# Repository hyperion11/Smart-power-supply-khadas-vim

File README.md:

# Smart-power-supply-khadas-vim
smart power supply for carpc based on khadas vim1 and rtd2662 scaler

https://youtu.be/VpjinB8Rm2o

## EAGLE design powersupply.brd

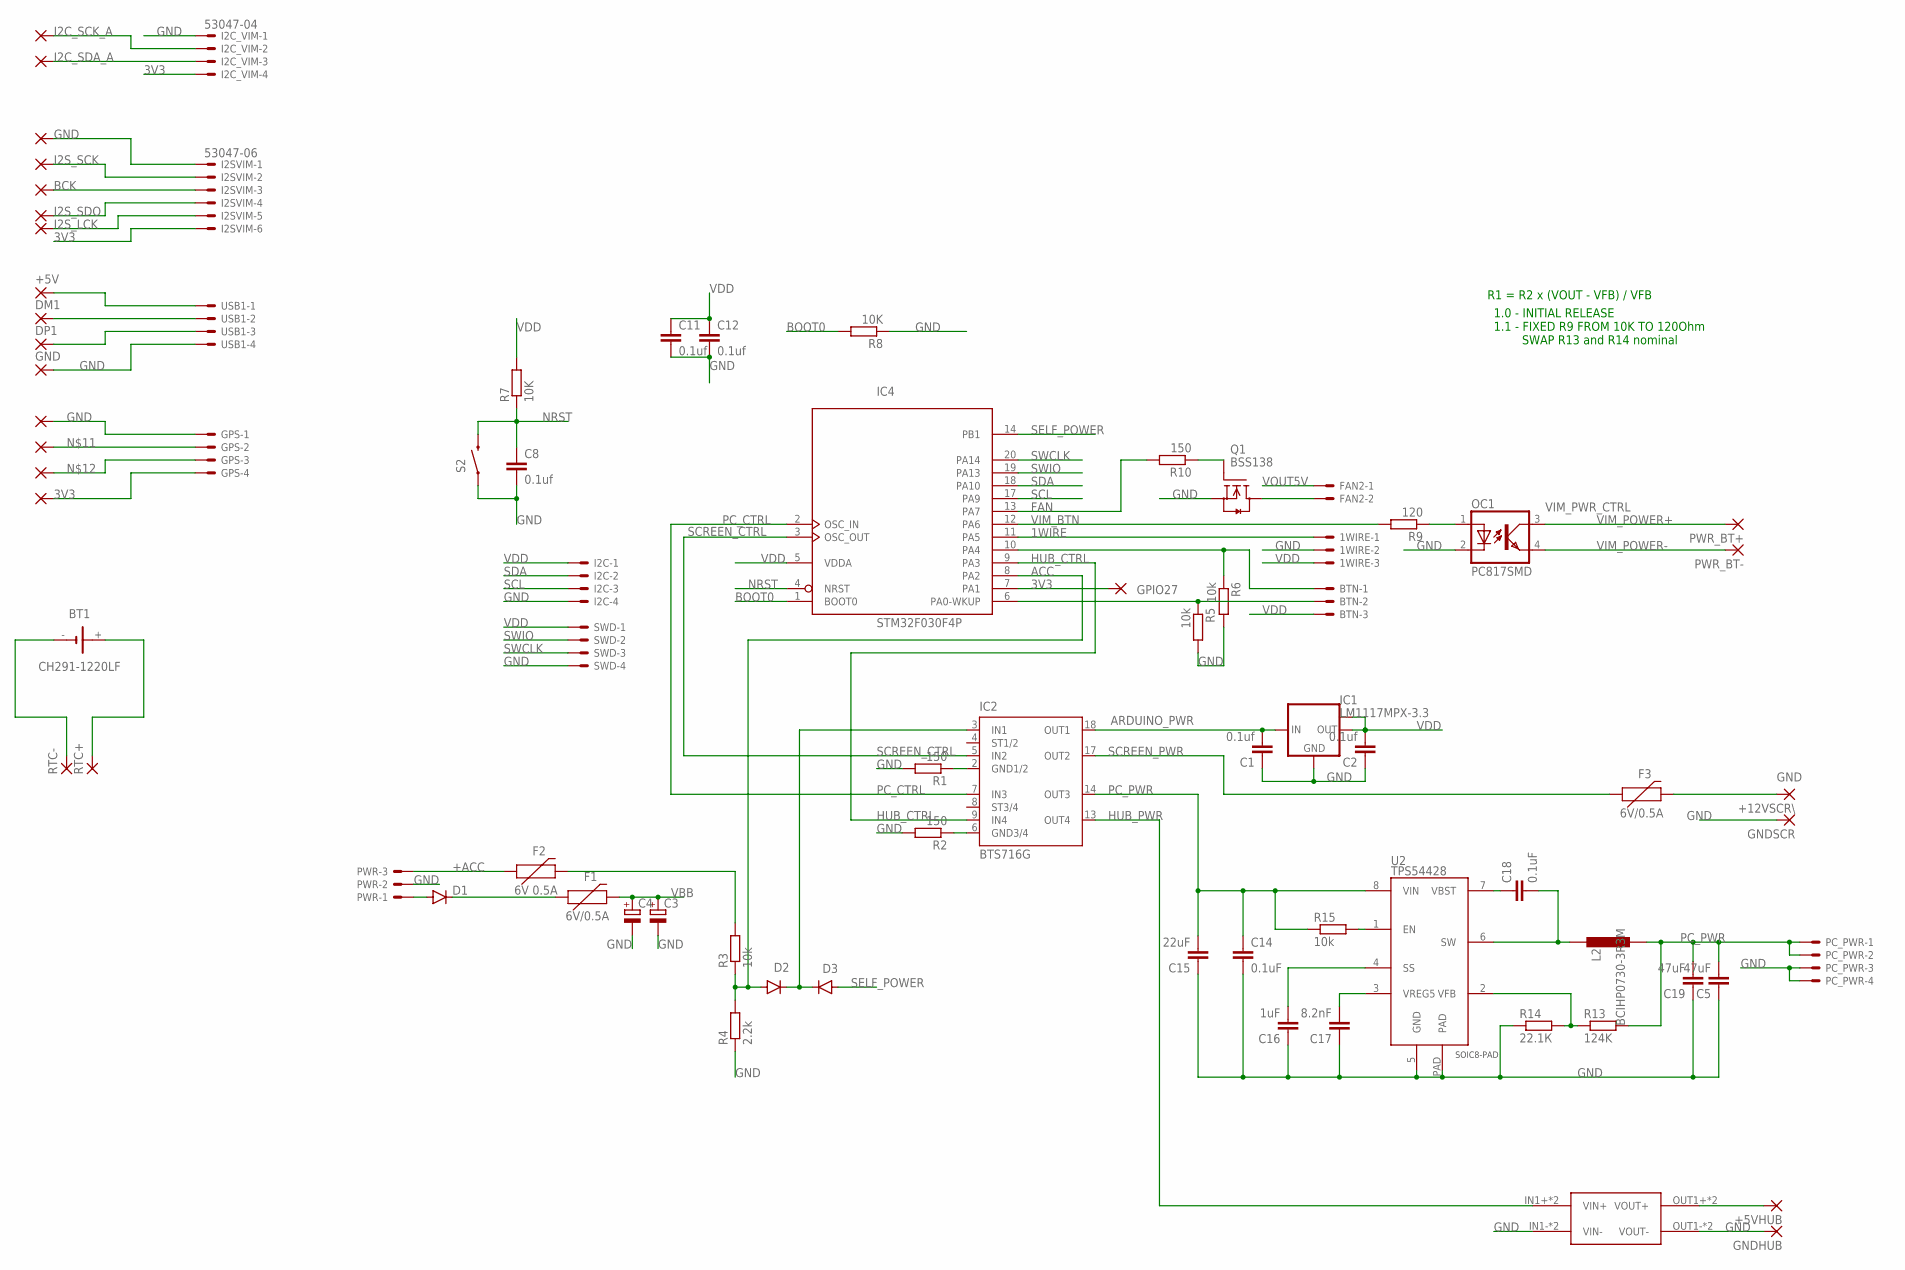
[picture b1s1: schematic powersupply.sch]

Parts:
1WIRE: 53047-03
3V3_1, 22, 23, 28, 29, 30, 31, 32: 1,6/0,8
+5V, +5VHUB, +12VSCR\: 1,6/0,8
BT1: CH291-1220LF
BTN: 53047-03
C1, C2, C8, C11, C12: 0.1uf; C0805; MPN CL21B104KBFNNNE
C3, C4: CPOL-EUUD-8X10; UD-8X10_NICHICON
C5, C19: 47uF; C1206; MPN CL31A476MPHNNNE
C14, C18: 0.1uF; C0805K; MPN CL21B104KBFNNNE
C15: 22uF; C0805; MPN CL31A226KAHNNNE
C16: 1uF; C0805K; MPN CL21B105KAFNNNE
C17: 8.2nF; C0805K; MPN CL21B822KBANNNC
D1: DIODE-SMB; SMB
D2, D3: DIODE-SOD323-W; SOD323-W
DM1: 1,6/0,8
DP1: 1,6/0,8
F1, F3: 6V/0.5A; 1206
F2: 6V 0.5A; 0805
FAN2: 53047-02
GND: 1,6/0,8
GNDGPS: 1,6/0,8
GNDHUB: 1,6/0,8
GNDSCR: 1,6/0,8
GPIO27: 1,6/0,8
GPS: 53047-04
I2C: i2c; 53047-04
I2C_VIM: 53047-04
I2SVIM: 53047-06
IC1: LM1117MPX-3.3; SOT223; MPN LM1117IMPX-3.3/NOPB
IC2: BTS716G; PG-DSO-20
IC4: STM32F030F4P; TSSOP20-I
L2: BCIHP0730-3R3M; VLS4045EX; MPN VLS5045EX-3R3N
OC1: PC817SMD; DIL04SMD; MPN PC817X2CSP9F
PC_PWR: i2c; 53047-04
PWR: JST-XH-03-PIN-ROUND-PAD; JST-XH-03-PACKAGE-ROUND-PAD
PWR_BT+: 1,6/0,8
PWR_BT-: 1,6/0,8
Q1: BSS138; SOT23
R1, R2, R10: 150; R0805
R3, R5, R6: 10k; R0805
R4: 2.2k; R0805
R7, R8: 10K; M0805
R9: 120; M0805
R13: 124K; M0805; MPN TR0805B22K1P0525Z
R14: 22.1К; M0805; MPN AR05BTCW1253
R15: 10k; M0805
RTC+: 1,6/0,8
RTC-: 1,6/0,8
RX: 1,6/0,8
S2: SWITCH-MOMENTARY-2-SMD-1101NE; TACTILE-SWITCH-1101NE
SWD: 53047-04
TX: 1,6/0,8
U2: TPS54428; PDSO-8
U$1: MP1584; DC-BRICK
USB1: 53047-04

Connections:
1WIRE: 1WIRE.1, IC4.11 (PA5)
3V3: 3V3_1.1, GPIO27.1, GPS.4, I2C_VIM.4, I2SVIM.6, IC4.7 (PA1)
+ACC: F2.2, R3.2
ACC: D2.A, IC4.8 (PA2), R3.1, R4.2
ARDUINO_PWR: C1.2, IC1.3 (IN), IC2.18 (OUT1)
BCK: 30.1, I2SVIM.3
BOOT0: IC4.1 (BOOT0), R8.2
FAN: IC4.13 (PA7), R10.2
GND: 1WIRE.2, 28.1, C1.1, C2.1, C3.-, C4.-, C5.1, C8.2, C11.2, C12.2, C14.2, C15.1, C16.1, C17.1, C19.1, GND.1, GNDGPS.1, GNDHUB.1, GNDSCR.1, GPS.1, I2C.4, I2C_VIM.1, I2SVIM.1, IC1.1 (GND), IC4.15 (GND), OC1.2 (C), PC_PWR.3, PC_PWR.4, PWR.2, Q1.2 (S), R1.2, R2.2, R4.1, R5.2, R6.2, R8.1, R14.1, S2.P$1 (1), SWD.4, U2.5 (GND), U2.PAD, U$1.IN1- (VIN-), U$1.IN2- (VIN-), U$1.OUT1- (VOUT-), U$1.OUT2- (VOUT-), USB1.4
HUB_CTRL: IC2.9 (IN4), IC4.9 (PA3)
HUB_PWR: IC2.13 (OUT4), U$1.IN1+ (VIN+), U$1.IN2+ (VIN+)
I2C_SCK_A: 22.1, I2C_VIM.2
I2C_SDA_A: 23.1, I2C_VIM.3
I2S_LCK: 32.1, I2SVIM.5
I2S_SCK: 29.1, I2SVIM.2
I2S_SDO: 31.1, I2SVIM.4
unnamed: IC2.2 (GND1/2), R1.1
unnamed: +5V.1, USB1.1
unnamed: FAN2.2, Q1.3 (D)
unnamed: D2.C, D3.C, IC2.3 (IN1)
unnamed: IC2.6 (GND3/4), R2.1
unnamed: BTN.1, IC4.10 (PA4), R6.1
unnamed: DM1.1, USB1.2
unnamed: DP1.1, USB1.3
unnamed: Q1.1 (G), R10.1
unnamed: BT1.-, RTC-.1
unnamed: GPS.2, RX.1
unnamed: GPS.3, TX.1
unnamed: BTN.2, IC4.6 (PA0-WKUP), R5.1
unnamed: F2.1, PWR.3
unnamed: BT1.+, RTC+.1
unnamed: D1.A, PWR.1
unnamed: +5VHUB.1, U$1.OUT1+ (VOUT+), U$1.OUT2+ (VOUT+)
unnamed: D1.C, F1.1
unnamed: +12VSCR\.1, F3.2
unnamed: C16.2, U2.4 (SS)
unnamed: C17.2, U2.3 (VREG5)
unnamed: C18.1, U2.7 (VBST)
unnamed: C18.2, L2.1, U2.6 (SW)
unnamed: R13.1, R14.2, U2.2 (VFB)
unnamed: R15.2, U2.1 (EN)
NRST: C8.1, IC4.4 (NRST), R7.1, S2.P$2 (2)
PC_CTRL: IC2.7 (IN3), IC4.2 (OSC_IN)
PC_PWR: C14.1, C15.2, IC2.14 (OUT3), R15.1, U2.8 (VIN)
SCL: I2C.3, IC4.17 (PA9)
SCREEN_CTRL: IC2.5 (IN2), IC4.3 (OSC_OUT)
SCREEN_PWR: F3.1, IC2.17 (OUT2)
SDA: I2C.2, IC4.18 (PA10)
SELF_POWER: D3.A, IC4.14 (PB1)
SWCLK: IC4.20 (PA14), SWD.3
SWIO: IC4.19 (PA13), SWD.2
VBB: C3.+, C4.+, F1.2, IC2.1 (VBB), IC2.10 (VBB), IC2.11 (VBB), IC2.12 (VBB), IC2.15 (VBB), IC2.16 (VBB), IC2.19 (VBB), IC2.20 (VBB)
VDD: 1WIRE.3, BTN.3, C2.2, C11.1, C12.1, I2C.1, IC1.2 (OUT), IC1.TAB (OUT1), IC4.5 (VDDA), IC4.16 (VDD), R7.2, SWD.1
VIM_BTN: IC4.12 (PA6), R9.2
VIM_POWER+: OC1.3 (COL), PWR_BT+.1
VIM_POWER-: OC1.4 (EMIT), PWR_BT-.1
VIM_PWR_CTRL: OC1.1 (A), R9.1
VOUT5V: C5.2, C19.2, FAN2.1, L2.2, PC_PWR.1, PC_PWR.2, R13.2

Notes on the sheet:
R1 = R2 x (VOUT - VFB) / VFB
1.0 - INITIAL RELEASE 1.1 - FIXED R9 FROM 10K TO 120Ohm SWAP R13 and R14 nominal

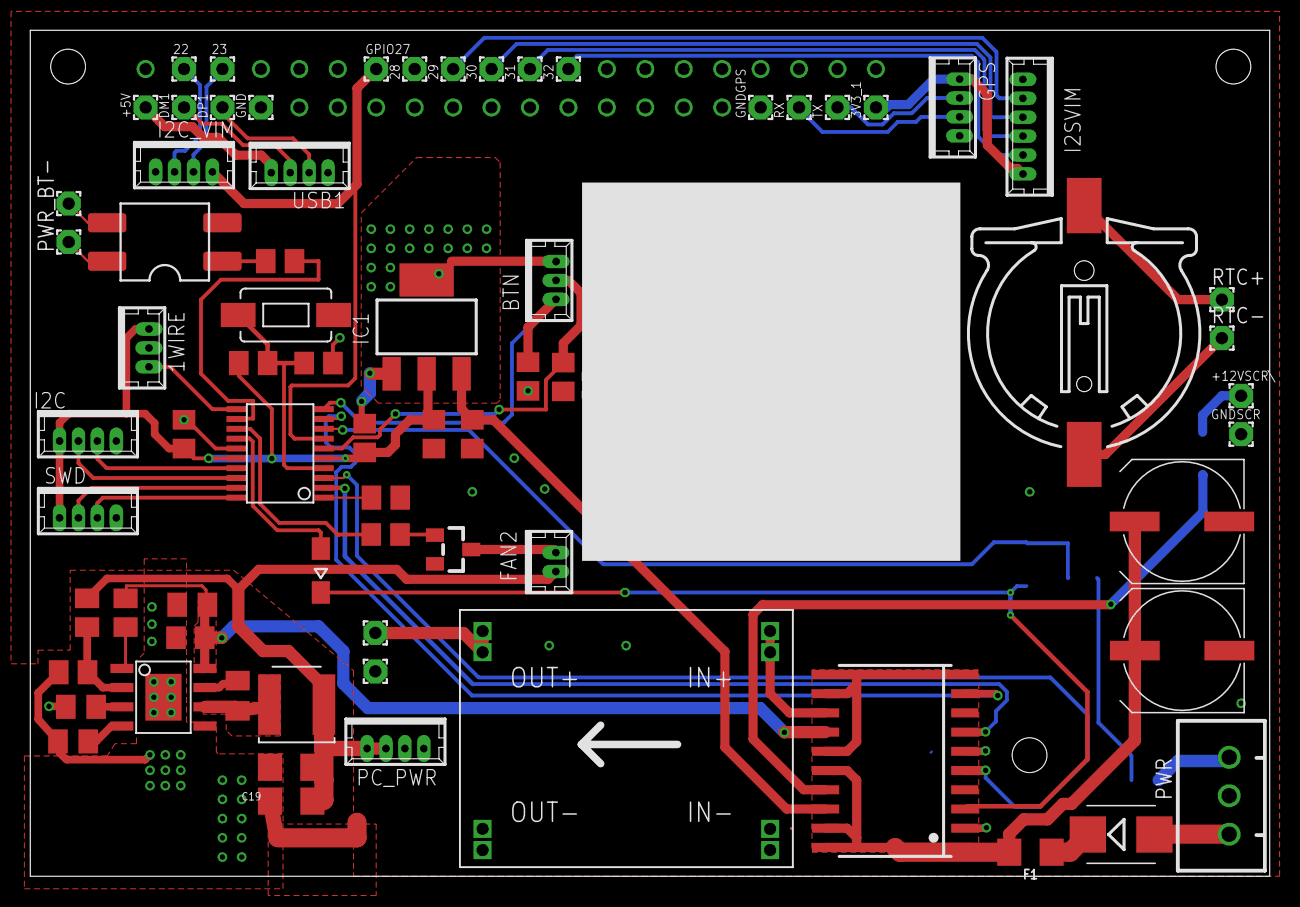
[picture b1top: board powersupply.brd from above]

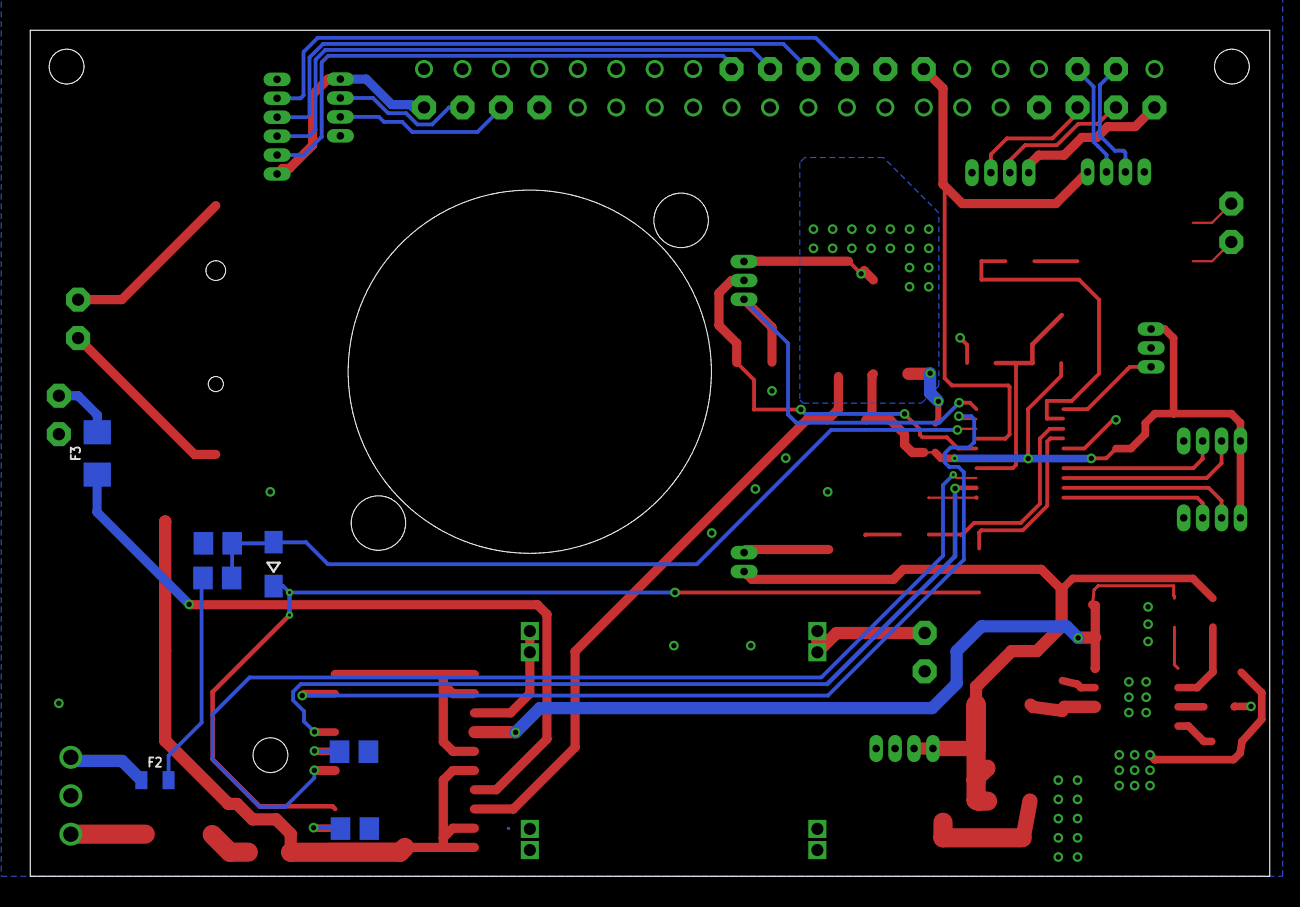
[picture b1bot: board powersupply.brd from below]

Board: 2 copper layers, 81.9 x 55.9 mm, 78 parts (7 on the bottom side), 58 nets.

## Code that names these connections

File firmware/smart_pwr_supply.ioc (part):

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Mcu.Name=STM32F030F4Px
Mcu.Package=TSSOP20
Mcu.UserName=STM32F030F4Px
PA0.GPIOParameters=GPIO_Label
PA0.GPIO_Label=BTN2
PA0.Signal=GPIO_Input
PA1.GPIOParameters=GPIO_Label
PA1.GPIO_Label=VIM_IN
PA1.Signal=GPIO_Input
PA13.Mode=Serial_Wire
PA13.Signal=SYS_SWDIO
PA14.Mode=Serial_Wire
PA14.Signal=SYS_SWCLK
PA2.Mode=IN2
PA2.Signal=ADC_IN2
PA3.GPIOParameters=GPIO_Label
PA3.GPIO_Label=HUB_PWR
PA3.Signal=GPIO_Output
PA4.GPIOParameters=GPIO_Label
PA4.GPIO_Label=BTN1
PA4.Signal=GPIO_Input
PA6.GPIOParameters=GPIO_Label
PA6.GPIO_Label=VIM_BTN
PA6.Signal=GPIO_Output
PA7.GPIOParameters=GPIO_Label
PA7.GPIO_Label=FAN
PA7.Signal=GPIO_Output
PB1.GPIOParameters=PinState,GPIO_Label
PB1.GPIO_Label=SELF_PWR
PB1.PinState=GPIO_PIN_SET
PB1.Signal=GPIO_Output
PF0-OSC_IN.GPIOParameters=GPIO_Label
PF0-OSC_IN.GPIO_Label=PC_PWR
PF0-OSC_IN.Signal=GPIO_Output
PF1-OSC_OUT.GPIOParameters=GPIO_Label
PF1-OSC_OUT.GPIO_Label=SCREEN_PWR
PF1-OSC_OUT.Signal=GPIO_Output
RCC.SYSCLKFreq_VALUE=48000000
RCC.SYSCLKSource=RCC_SYSCLKSOURCE_PLLCLK
board=custom

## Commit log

2019-08-02 init commit
2020-01-21 фиксы схемы
    R9 FROM 10K TO 120Ohm
    SWAP R13 and R14 nominal
2020-01-21 комменты+таймеры
2020-03-22 pre-release
2020-03-22 pre release
2020-03-24 pre-pre2
    Фикс просыпания (не включался кулер)
    Почти все готово для тестирования

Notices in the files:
parts and their libraries:
m-pad-2.1: License : GNU General Public License version 2 (see bottom)
SparkFun-Fuses: Licensing: Creative Commons ShareAlike 4.0 International - https://creativecommons.org/licenses/by-sa/4.0
